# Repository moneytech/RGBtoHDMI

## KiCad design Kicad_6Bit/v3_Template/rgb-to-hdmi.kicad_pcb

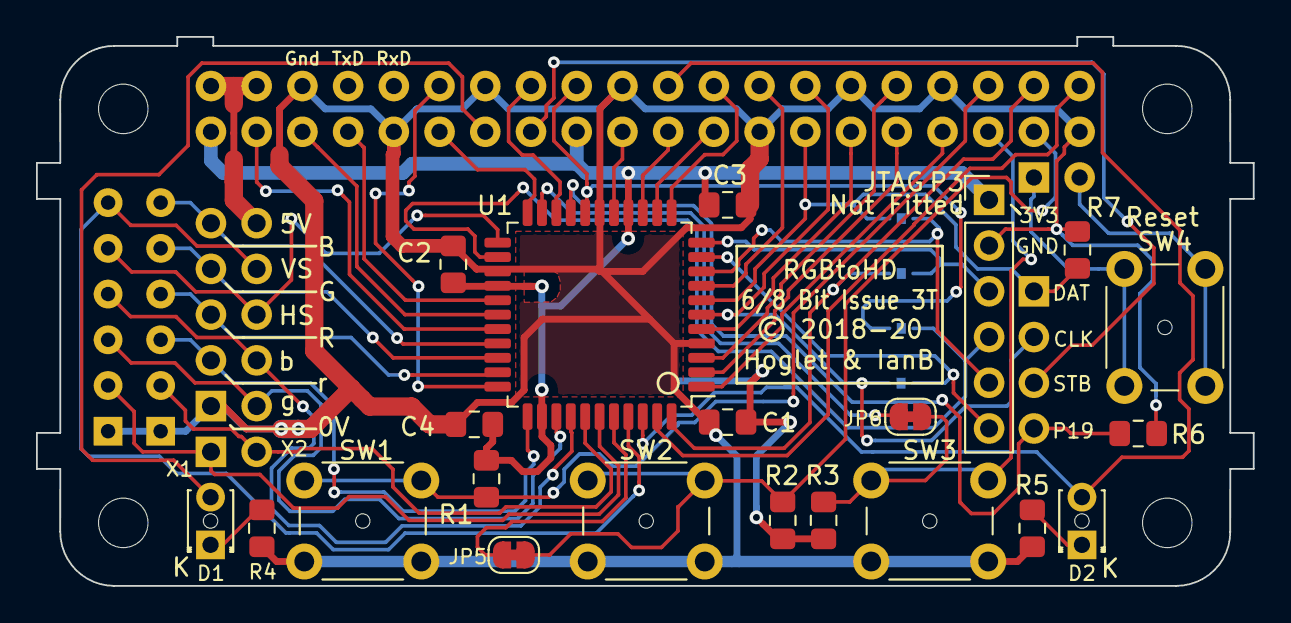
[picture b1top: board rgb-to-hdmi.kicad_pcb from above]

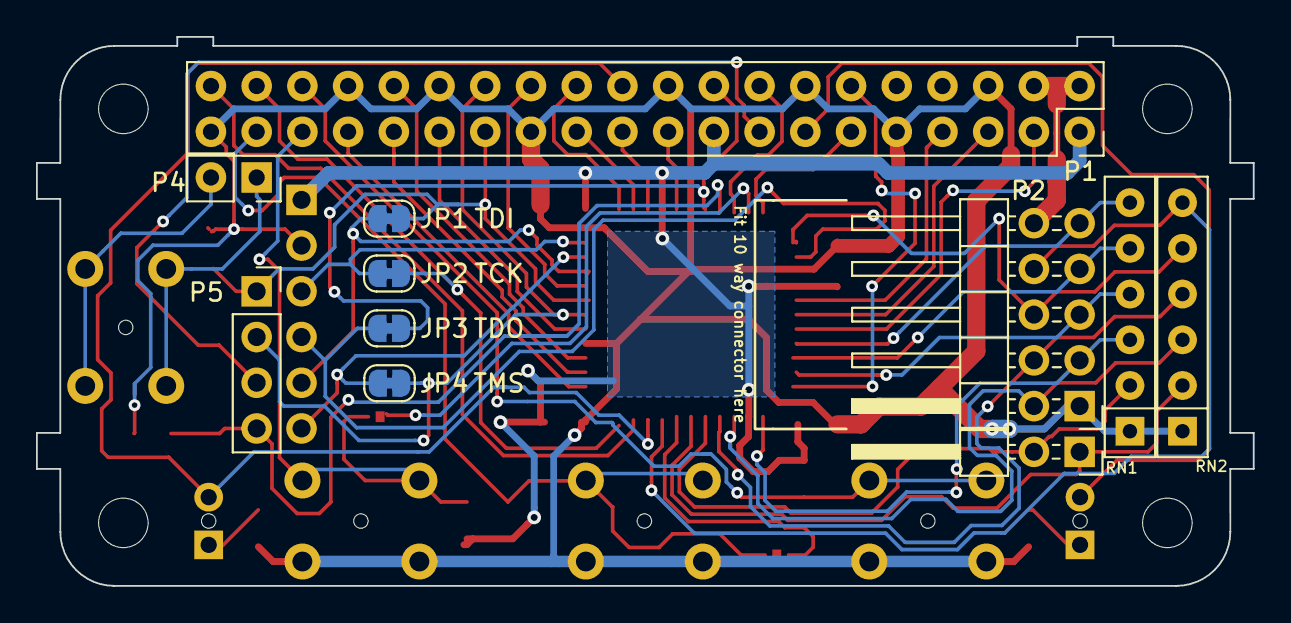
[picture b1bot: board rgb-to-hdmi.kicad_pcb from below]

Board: 2 copper layers, 67.6 x 30.5 mm, 38 parts (11 on the bottom side), 50 nets.

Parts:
 : mountinghole_1mm
 #2,  #3,  #4,  #5,  #6: mountinghole_1mm
C1: 10uF; C_0805_2012Metric_Pad1.15x1.40mm_HandSolder
C2, C3, C4: 100nF; C_0805_2012Metric_Pad1.15x1.40mm_HandSolder
D1, D2: LED; LED_D1.8mm_W3.3mm_H2.4mm_Custom
J2: Conn_02x01; PinHeader_2x01_P2.54mm_Horizontal
JP1, JP2, JP3, JP4, JP5, JP6: SolderJumper_2_Bridged; SolderJumper-2_P1.3mm_Bridged_RoundedPad1.0x1.5mm
P1: CONN_02X20; PinSocket_2x20_P2.54mm_Vertical_Custom
P2: Conn_02x05_Odd_Even; PinHeader_2x05_P2.54mm_Horizontal
P3: Conn_01x06; PinHeader_1x06_P2.54mm_Vertical
P4: CONN_01X02; PinSocket_1x02_P2.54mm_Vertical_Custom
P5: Conn_01x04; PinSocket_1x04_P2.54mm_Vertical
R1, R2, R3, R4, R5, R7: 1K; R_0805_2012Metric_Pad1.15x1.40mm_HandSolder
R6: 10K; R_0805_2012Metric_Pad1.15x1.40mm_HandSolder
RN1, RN2: 4K7; R_Array_SIP6
SW1, SW2, SW3, SW4: SW_PUSH; SW_PUSH_6mm_H5mm
U1: XC9572XL-VQFP44; LQFP-44_10x10mm_P0.8mm

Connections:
/3V3: C1.1, C2.1, C3.1, C4.1, P1.1, P1.17, P3.1, R1.1, R2.1, R3.1, U1.15, U1.26, U1.35
/BBLUE: P2.4, RN2.4, U1.37
/BGREEN: P2.2, RN2.3, U1.36
/BLUE: P2.9, RN1.6, U1.30
/BRED: P2.3, RN1.3, U1.34
/DETECT: P5.4, R6.1, U1.19
/GND: C1.2, C2.2, C3.2, C4.2, P1.6, P1.9, P1.14, P1.20, P1.25, P1.30, P1.34, P1.39, P2.1, P3.2, R4.2, R5.2, R6.2, R7.2, RN1.1, RN2.1, SW1.1, SW2.1, SW3.1, U1.4, U1.17, U1.25
/GPIO0: JP1.1, P1.27, P5.1, R7.1, U1.7
/GPIO1: JP4.1, P1.28, P5.2, U1.6
/GPIO2: P1.3, U1.29
/GPIO3: P1.5, U1.28
/GPIO4: P1.7, U1.27
/GPIO5: P1.29, U1.5
/GPIO6: P1.31, U1.2
/GPIO7: P1.26, U1.8
/GPIO8: P1.24, U1.12
/GPIO9: P1.21, U1.14
/GPIO10: P1.19, U1.16
/GPIO11: P1.23, U1.13
/GPIO12: P1.32, U1.3
/GPIO13: P1.33, U1.1
/GPIO16: P1.36, R1.2, SW1.2
/GPIO17: P1.11, U1.22
/GPIO18: P1.12, U1.33
/GPIO19: JP6.2, P1.35, R3.2, SW3.2
/GPIO20: JP2.1, P1.38, U1.44
/GPIO21: P1.40, U1.43
/GPIO22: P1.15, P5.3
/GPIO23: P1.16, U1.20
/GPIO24: JP3.1, P1.18, U1.18
/GPIO25: D2.2, P1.22, U1.42
/GPIO26: JP5.2, P1.37, R2.2, SW2.2
/GPIO27: D1.2, P1.13
/GREEN: P2.7, RN1.5, U1.31
/RED: P2.5, RN1.4, U1.32
/SYNC: P2.6, RN2.5, U1.23
/TCK: JP2.2, P3.3, U1.11
/TDI: JP1.2, P3.5, U1.9
/TDO: JP3.2, P3.4, U1.24
/TMS: JP4.2, P3.6, U1.10
/VCC: P1.2, P1.4, P2.10
/VSYNC: P2.8, RN2.6, U1.41
/X1: J2.1, RN2.2, U1.39
/X2: J2.2, RN1.2, U1.38
/X3: JP5.1, U1.40
/X4: JP6.1, U1.21
unnamed: D1.1, R4.1
unnamed: D2.1, R5.1
unnamed: P4.1, SW4.2
unnamed: P4.2, SW4.1

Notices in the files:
Kicad_6Bit/v3_Template/rgb-to-hdmi.kicad_pcb:
© 2018-20
